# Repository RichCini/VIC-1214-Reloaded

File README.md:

# VIC-1214-Reloaded
Reimplementation of a voice synthesizer board I built in 1981.

The voice synthsizer is a user-port peripheral based on
a circuit design from the original Radio Shack/GI
data sheet (my original design), an article in BYTE (and
for which I can't find the reference; I only have the scan),
and a circuit in the Commodore 64 Interfacing Blue Book (which
had a nice test program). There is a project called retroSpeak
from jbeuckm (albeit an add-on for a Raspberry Pi) that uses an
external programmable clock rather than a crystal.

The Canonical List of Commodore Products lists a VIC-1214
Speech Synthesizer cartridge, but I have not been able to
locate any information on it. Several 3rd party companies
made an expansion port cartridge synthisizer such as the
VicTalker (SSI263 chip), the Adman (SP0256), the
Chatterbox, and the PPP SpeakEasy (SSI).

I tried a using a replacable TTL oscillator rather than
a crystal with the coupling circuit from jbeuckm's design,
but it didn't work. I suspect that the signal phase is
wrong, but until I test it with my Silgent waveform
generator, I won't know. I think it needs an inverted
clock in order to work. So, the existing design uses
the tried-and-true crystal for now. Changing the crystal
frequency will change the pitch of the voice, so even a
colorburst crystal (3.59MHz) will work.

I had a few sample boards made and it works flawlessly with
the LM386 amplifier. Glad to see it worked the first time!

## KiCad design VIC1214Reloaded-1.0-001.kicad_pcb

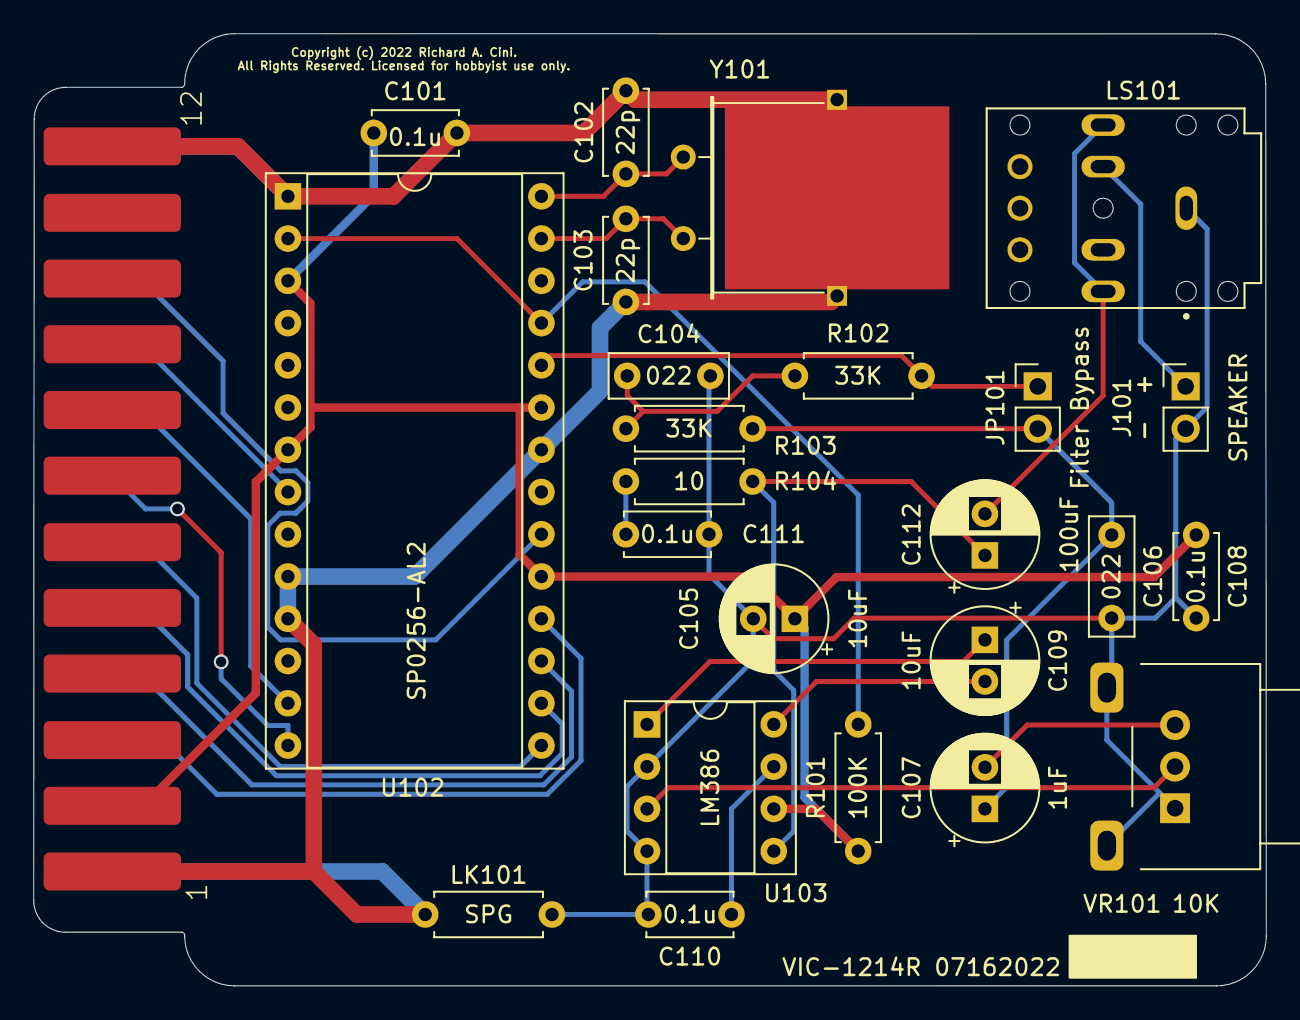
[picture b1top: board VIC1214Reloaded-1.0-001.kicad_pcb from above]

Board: 2 copper layers, 74.1 x 57.3 mm, 25 parts (0 on the bottom side), 26 nets.

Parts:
C101, C108, C110, C111: 0.1u; C_Disc_D5.0mm_W2.5mm_P5.00mm
C102, C103: 22p; C_Disc_D5.0mm_W2.5mm_P5.00mm
C104, C106: 022; C_Disc_D7.0mm_W2.5mm_P5.00mm
C105, C109: 10uF; CP_Radial_D6.3mm_P2.50mm
C107: 1uF; CP_Radial_D6.3mm_P2.50mm
C112: 100uF; CP_Radial_D6.3mm_P2.50mm
J101: SJ-3568N; CUI_SJ-3568N
JP101: Filter Bypass; PinHeader_1x02_P2.54mm_Vertical
LK101: Link; R_Axial_DIN0207_L6.3mm_D2.5mm_P7.62mm_Horizontal
LS101: SPEAKER; PinHeader_1x02_P2.54mm_Vertical
R101: 100K; R_Axial_DIN0207_L6.3mm_D2.5mm_P7.62mm_Horizontal
R102, R103: 33K; R_Axial_DIN0207_L6.3mm_D2.5mm_P7.62mm_Horizontal
R104: 10; R_Axial_DIN0207_L6.3mm_D2.5mm_P7.62mm_Horizontal
U101: MA156-12-2; MA156-12-2-Peripheral
U102: SP0256-AL2; DIP-28_W15.24mm_Socket
U103: LM386; DIP-8_W7.62mm_Socket
VR101: 10K; Potentiometer_Alps_RK09L_Single_Horizontal
Y101: 3.12MHz; Crystal_HC49-U_Horizontal_1EP_style2

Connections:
GND: C101.2, C102.2, C103.2, LK101.1, U101.1, U101.12, U101.A, U101.N, U102.1 (GND), U102.10 (A8), U102.11 (A7), U102.22 (TEST), Y101.3
GNDA: C104.2, C105.2, C106.2, C108.2, C110.2, C111.2, J101.1, LK101.2, LS101.2, U103.2 (-), U103.4 (GND), VR101.1, VR101.MP (MountPin)
unnamed: C102.1, U102.28 (XTAL2), Y101.2
unnamed: C103.1, U102.27 (XTAL1), Y101.1
unnamed: C104.1, R102.2, R103.1
unnamed: C106.1, C107.1, JP101.2 (B), R103.2
unnamed: C107.2, VR101.3
unnamed: C109.1, U103.1 (GAIN)
unnamed: C109.2, U103.8 (GAIN)
unnamed: C110.1, U103.7 (BYPASS)
unnamed: C111.1, R104.1
unnamed: C112.1, R104.2, U103.5
unnamed: C112.2, J101.2, J101.3
unnamed: J101.10, LS101.1
unnamed: JP101.1 (A), R102.1, U102.24 (DIG_OUT)
unnamed: R101.1, U102.2 (~RESET), U102.25 (~SBY_RESET)
unnamed: U103.3 (+), VR101.2
PB0: U101.C, U102.18 (A1)
PB1: U101.D, U102.17 (A2)
PB2: U101.E, U102.16 (A3)
PB3: U101.F, U102.15 (A4)
PB4: U101.H, U102.14 (A5)
PB5: U101.J, U102.13 (A6)
PB6: U101.K, U102.8 (SBY)
PB7: U101.L, U102.20 (~ALD)
VCC: C101.1, C105.1, C108.1, R101.2, U101.2, U102.3 (ROM_DIS), U102.7 (VCC), U102.19 (SE), U102.23 (VD1), U103.6 (V+)

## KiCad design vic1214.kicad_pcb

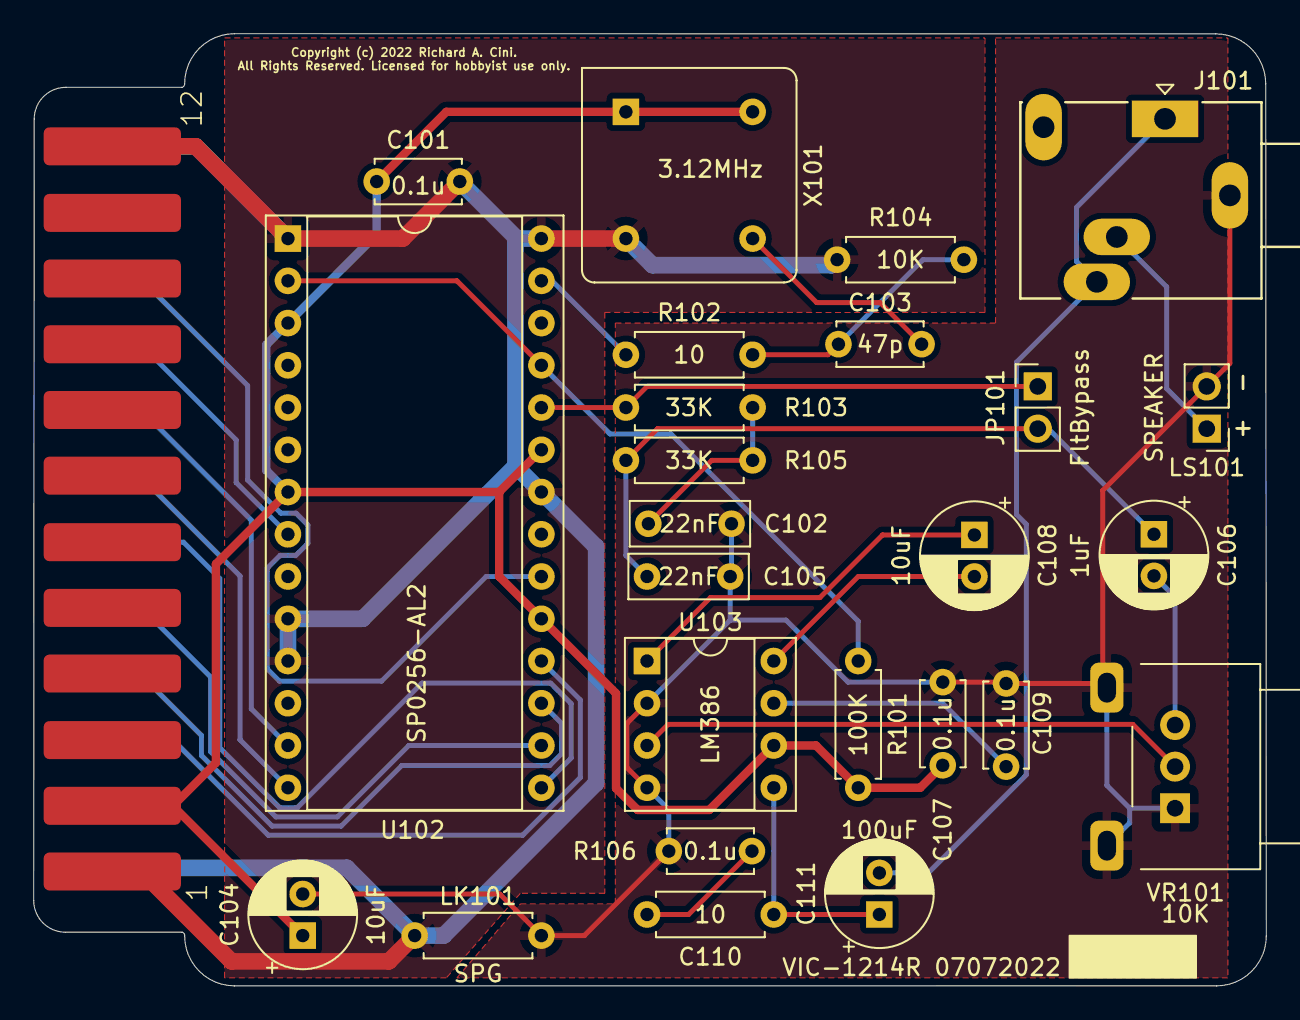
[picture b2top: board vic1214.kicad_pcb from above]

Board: 2 copper layers, 74.1 x 57.3 mm, 26 parts (0 on the bottom side), 27 nets.

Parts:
C101, C107, C109, C110: 0.1u; C_Disc_D5.0mm_W2.5mm_P5.00mm
C102, C105: 22nF; C_Disc_D7.0mm_W2.5mm_P5.00mm
C103: 47p; C_Disc_D5.0mm_W2.5mm_P5.00mm
C104, C108: 10uF; CP_Radial_D6.3mm_P2.50mm
C106: 1uF; CP_Radial_D6.3mm_P2.50mm
C111: 100uF; CP_Radial_D6.3mm_P2.50mm
J101: JACK 3.5MM; Jack_3.5mm_Ledino_KB3SPRS_Horizontal
JP101: FltBypass; PinHeader_1x02_P2.54mm_Vertical
LK101: Link; R_Axial_DIN0207_L6.3mm_D2.5mm_P7.62mm_Horizontal
LS101: SPEAKER; PinHeader_1x02_P2.54mm_Vertical
R101: 100K; R_Axial_DIN0207_L6.3mm_D2.5mm_P7.62mm_Horizontal
R102, R106: 10; R_Axial_DIN0207_L6.3mm_D2.5mm_P7.62mm_Horizontal
R103, R105: 33K; R_Axial_DIN0207_L6.3mm_D2.5mm_P7.62mm_Horizontal
R104: 10K; R_Axial_DIN0207_L6.3mm_D2.5mm_P7.62mm_Horizontal
U101: MA156-12-2; MA156-12-2-Peripheral
U102: SP0256-AL2; DIP-28_W15.24mm_Socket
U103: LM386; DIP-8_W7.62mm_Socket
VR101: 10K; Potentiometer_Alps_RK09L_Single_Horizontal
X101: 3.12MHz; Oscillator_DIP-8

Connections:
GND: C101.2, LK101.1, R104.2, U101.1, U101.12, U101.A, U101.N, U102.1 (GND), U102.10 (A8), U102.11 (A7), U102.22 (TEST), U102.28 (XTAL2), X101.4 (GND)
GNDA: C102.2, C104.2, C105.2, C107.2, C109.2, C110.2, J101.S, LK101.2, LS101.2, U103.2 (-), U103.4 (GND), VR101.1, VR101.MP (MountPin)
unnamed: C102.1, R103.2, R105.1
unnamed: C103.1, R102.1, R104.1
unnamed: C103.2, X101.5 (OUT)
unnamed: C105.1, C106.1, JP101.2 (B), R105.2
unnamed: C106.2, VR101.3
unnamed: C108.1, U103.1 (GAIN)
unnamed: C108.2, U103.8 (GAIN)
unnamed: C109.1, U103.7 (BYPASS)
unnamed: C110.1, R106.1
unnamed: C111.1, R106.2, U103.5
unnamed: C111.2, J101.R, J101.T
unnamed: J101.RN, LS101.1
unnamed: JP101.1 (A), R103.1, U102.24 (DIG_OUT)
unnamed: R101.1, U102.2 (~RESET), U102.25 (~SBY_RESET)
unnamed: R102.2, U102.27 (XTAL1)
unnamed: U103.3 (+), VR101.2
PB0: U101.C, U102.18 (A1)
PB1: U101.D, U102.17 (A2)
PB2: U101.E, U102.16 (A3)
PB3: U101.F, U102.15 (A4)
PB4: U101.H, U102.14 (A5)
PB5: U101.J, U102.13 (A6)
PB6: U101.K, U102.8 (SBY)
PB7: U101.L, U102.20 (~ALD)
VCC: C101.1, C104.1, C107.1, R101.2, U101.2, U102.3 (ROM_DIS), U102.7 (VCC), U102.19 (SE), U102.23 (VD1), U103.6 (V+), X101.1 (EN), X101.8 (Vcc)

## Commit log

2022-07-16 Add files via upload
    Renamed certain sub-files; changed the component for the audio jack.

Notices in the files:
VIC1214Reloaded-1.0-001.kicad_pcb:
Copyright (c) 2022 Richard A. Cini.
All Rights Reserved. Licensed for hobbyist use only.
